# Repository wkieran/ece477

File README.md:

# ece477

## mimidrums

## prototyping
(1) mic_tutorial : microphone + SD

    if button is pressed once (EXTI_GPIO), mic is recording.
    if button is pressed once more, mic stops recording. And save audio files into SD as wav file.

## docs

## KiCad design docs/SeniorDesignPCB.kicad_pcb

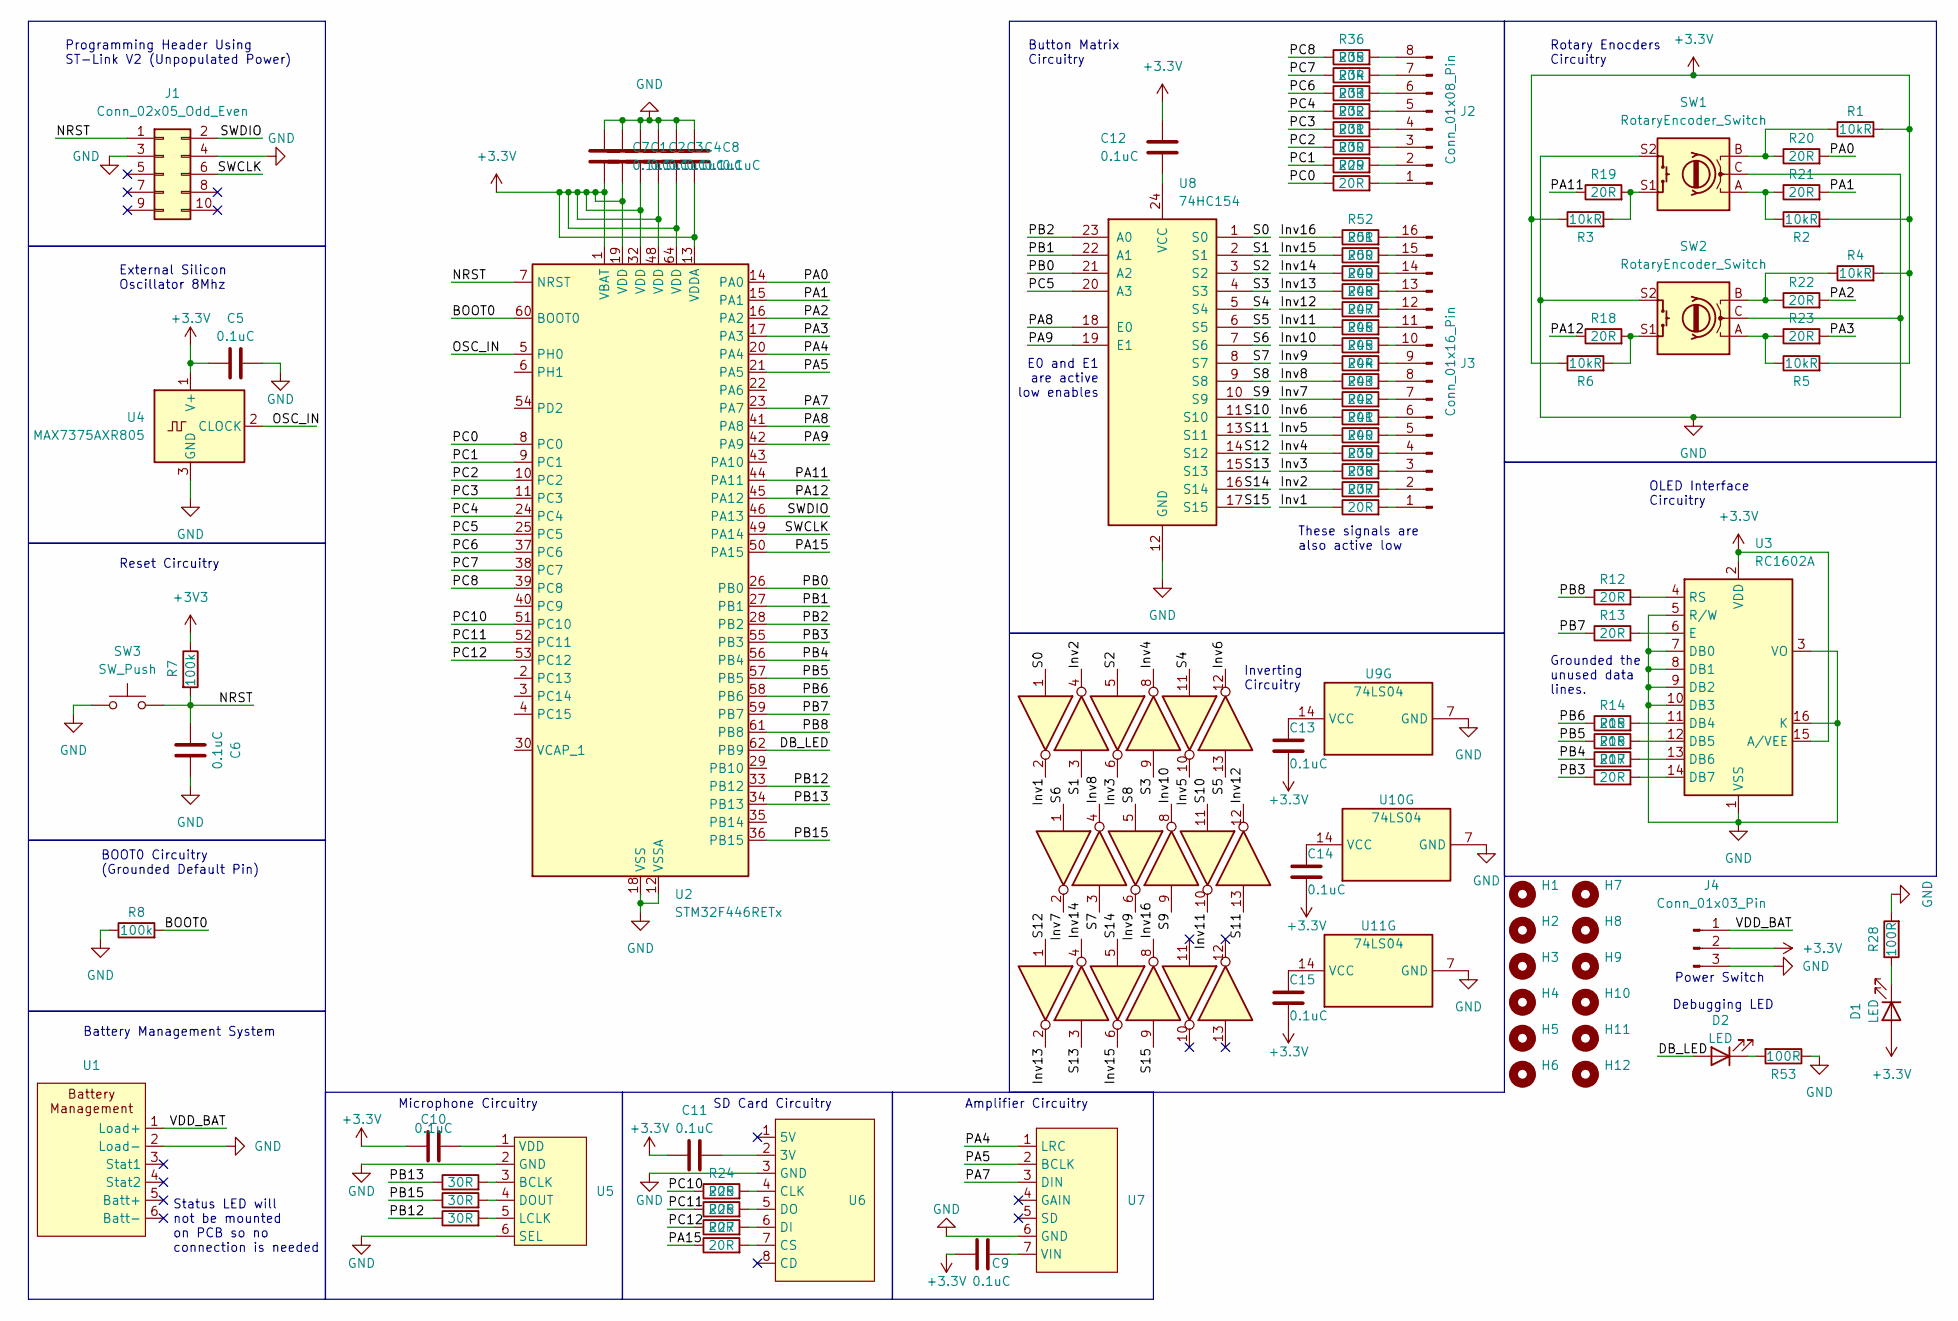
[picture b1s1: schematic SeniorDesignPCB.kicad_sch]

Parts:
C1, C2, C3, C4, C5, C6, C7, C8, C9, C10, C11, C12, C13, C14, C15: 0.1uC; C_0805_2012Metric_Pad1.18x1.45mm_HandSolder
D1: LED; D_5KP_P7.62mm_Vertical_AnodeUp
D2: LED; D_0805_2012Metric
H1, H2, H3, H4, H5, H6, H7, H8: MountingHole; MountingHole_2.2mm_M2
H9, H10, H11, H12: MountingHole; MountingHole_2.5mm
J1: Conn_02x05_Odd_Even; PinHeader_2x05_P2.54mm_Vertical
J2: Conn_01x08_Pin; PinHeader_1x08_P2.54mm_Vertical
J3: Conn_01x16_Pin; PinHeader_1x16_P2.54mm_Vertical
J4: Conn_01x03_Pin; PinHeader_1x03_P2.54mm_Vertical
R1, R2, R3, R4, R5, R6: 10kR; R_0805_2012Metric_Pad1.20x1.40mm_HandSolder
R7, R8: 100k; R_0805_2012Metric_Pad1.20x1.40mm_HandSolder
R9, R10, R11: 30R; R_0805_2012Metric_Pad1.20x1.40mm_HandSolder
R12, R13, R14, R15, R16, R17, R18, R19, R20, R21, R22, R23, R24, R25, R26, R27, R29, R30, R31, R32, R33, R34, R35, R36, R37, R38, R39, R40, R41, R42, R43, R44, R45, R46, R47, R48, R49, R50, R51, R52: 20R; R_0805_2012Metric_Pad1.20x1.40mm_HandSolder
R28, R53: 100R; R_0805_2012Metric_Pad1.20x1.40mm_HandSolder
SW1, SW2: RotaryEncoder_Switch; RotaryEncoder_Alps_EC11E-Switch_Vertical_H20mm
SW3: SW_Push; SW_Push_1P1T_NO_6x6mm_H9.5mm
U1, U5: PinHeader_1x06_P2.54mm_Vertical
U2: STM32F446RETx; LQFP-64_10x10mm_P0.5mm
U3: RC1602A; PinHeader_1x16_P2.54mm_Vertical
U4: MAX7375AXR805; SOT-323_SC-70
U6: PinHeader_1x08_P2.54mm_Vertical
U7: PinHeader_1x07_P2.54mm_Vertical
U8: 74HC154; DIP-24_W7.62mm
U9, U10, U11: 74LS04; DIP-14_W7.62mm

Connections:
+3.3V: C1.2, C2.2, C3.2, C4.2, C5.1, C7.2, C8.2, C9.1, C10.1, C11.1, C12.1, C13.2, C14.2, C15.2, D1.2 (A), J4.2, R1.2, R2.2, R3.1, R4.2, R5.2, R6.1, U2.1 (VBAT), U2.13 (VDDA), U2.19 (VDD), U2.32 (VDD), U2.48 (VDD), U2.64 (VDD), U3.2 (VDD), U3.15 (A/VEE), U4.1 (V+)
+3V3: R7.1
/BOOT0: R8.2, U2.60 (BOOT0)
/DB_LED: D2.2 (A), U2.62 (PB9)
/Inv1: R37.1, U9.2
/Inv2: R38.1, U9.4
/Inv3: R39.1, U9.6
/Inv4: R40.1, U9.8
/Inv5: R41.1, U9.10
/Inv6: R42.1, U9.12
/Inv7: R43.1, U10.2
/Inv8: R44.1, U10.4
/Inv9: R45.1, U10.6
/Inv10: R46.1, U10.8
/Inv11: R47.1, U10.10
/Inv12: R48.1, U10.12
/Inv13: R49.1, U11.2
/Inv14: R50.1, U11.4
/Inv15: R51.1, U11.6
/Inv16: R52.1, U11.8
/NRST: C6.1, J1.1, R7.2, SW3.2, U2.7 (NRST)
/OSC_IN: U2.5 (PH0), U4.2 (CLOCK)
/PA0: R20.2, U2.14 (PA0)
/PA1: R21.2, U2.15 (PA1)
/PA2: R22.2, U2.16 (PA2)
/PA3: R23.2, U2.17 (PA3)
/PA4: U2.20 (PA4), U7.1 (LRC)
/PA5: U2.21 (PA5), U7.2 (BCLK)
/PA7: U2.23 (PA7), U7.3 (DIN)
/PA8: U2.41 (PA8), U8.18 (E0)
/PA9: U2.42 (PA9), U8.19 (E1)
/PA11: R19.1, U2.44 (PA11)
/PA12: R18.1, U2.45 (PA12)
/PA15: R27.1, U2.50 (PA15)
/PB0: U2.26 (PB0), U8.21 (A2)
/PB1: U2.27 (PB1), U8.22 (A1)
/PB2: U2.28 (PB2), U8.23 (A0)
/PB3: R17.1, U2.55 (PB3)
/PB4: R16.1, U2.56 (PB4)
/PB5: R15.1, U2.57 (PB5)
/PB6: R14.1, U2.58 (PB6)
/PB7: R13.1, U2.59 (PB7)
/PB8: R12.1, U2.61 (PB8)
/PB12: R11.1, U2.33 (PB12)
/PB13: R9.1, U2.34 (PB13)
/PB15: R10.1, U2.36 (PB15)
/PC0: R29.1, U2.8 (PC0)
/PC1: R30.1, U2.9 (PC1)
/PC2: R31.1, U2.10 (PC2)
/PC3: R32.1, U2.11 (PC3)
/PC4: R33.1, U2.24 (PC4)
/PC5: U2.25 (PC5), U8.20 (A3)
/PC6: R34.1, U2.37 (PC6)
/PC7: R35.1, U2.38 (PC7)
/PC8: R36.1, U2.39 (PC8)
/PC10: R24.1, U2.51 (PC10)
/PC11: R25.1, U2.52 (PC11)
/PC12: R26.1, U2.53 (PC12)
/S0: U8.1 (S0), U9.1
/S1: U8.2 (S1), U9.3
/S2: U8.3 (S2), U9.5
/S3: U8.4 (S3), U9.9
/S4: U8.5 (S4), U9.11
/S5: U8.6 (S5), U9.13
/S6: U8.7 (S6), U10.1
/S7: U8.8 (S7), U10.3
/S8: U8.9 (S8), U10.5
/S9: U8.10 (S9), U10.9
/S10: U8.11 (S10), U10.11
/S11: U8.13 (S11), U10.13
/S12: U8.14 (S12), U11.1
/S13: U8.15 (S13), U11.3
/S14: U8.16 (S14), U11.5
/S15: U8.17 (S15), U11.9
/SWCLK: J1.6, U2.49 (PA14)
/SWDIO: J1.2, U2.46 (PA13)
/VDD_BAT: J4.1, U1.1 (Load+)
GND: C1.1, C2.1, C3.1, C4.1, C5.2, C6.2, C7.1, C8.1, J1.3, J1.4, J4.3, R8.1, R28.2, R53.1, SW1.C, SW1.S2, SW2.C, SW2.S2, SW3.1, U1.2 (Load-), U2.12 (VSSA), U2.18 (VSS), U2.31 (VSS), U2.47 (VSS), U2.63 (VSS), U3.1 (VSS), U3.3 (VO), U3.5 (R/W), U3.7 (DB0), U3.8 (DB1), U3.9 (DB2), U3.10 (DB3), U3.16 (K), U4.3 (GND), U5.2 (GND), U5.6 (SEL), U6.3 (GND), U7.6 (GND), U8.12 (GND), U9.7 (GND), U10.7 (GND), U11.7 (GND)
unnamed: D1.1 (K), R28.1
unnamed: D2.1 (K), R53.2
unnamed: J2.1, R29.2
unnamed: J2.2, R30.2
unnamed: J2.3, R31.2
unnamed: J2.4, R32.2
unnamed: J2.5, R33.2
unnamed: J2.6, R34.2
unnamed: J2.7, R35.2
unnamed: J2.8, R36.2
unnamed: J3.1, R37.2
unnamed: J3.2, R38.2
unnamed: J3.3, R39.2
unnamed: J3.4, R40.2
unnamed: J3.5, R41.2
unnamed: J3.6, R42.2
unnamed: J3.7, R43.2
unnamed: J3.8, R44.2
unnamed: J3.9, R45.2
unnamed: J3.10, R46.2
unnamed: J3.11, R47.2
unnamed: J3.12, R48.2
unnamed: J3.13, R49.2
unnamed: J3.14, R50.2
unnamed: J3.15, R51.2
unnamed: J3.16, R52.2
unnamed: R1.1, R20.1, SW1.B
unnamed: R2.1, R21.1, SW1.A
unnamed: R6.2, R18.2, SW2.S1
unnamed: R3.2, R19.2, SW1.S1
unnamed: R4.1, R22.1, SW2.B
unnamed: R5.1, R23.1, SW2.A
unnamed: R14.2, U3.11 (DB4)
unnamed: R15.2, U3.12 (DB5)
unnamed: R16.2, U3.13 (DB6)
unnamed: R17.2, U3.14 (DB7)
unnamed: R13.2, U3.6 (E)
unnamed: R12.2, U3.4 (RS)
unnamed: R9.2, U5.3 (BCLK)
unnamed: R10.2, U5.4 (DOUT)
unnamed: R11.2, U5.5 (LCLK)
unnamed: C10.2, U5.1 (VDD)
unnamed: C11.2, U6.2 (3V)
unnamed: R24.2, U6.4 (CLK)
unnamed: R27.2, U6.7 (CS)
unnamed: R26.2, U6.6 (DI)
unnamed: R25.2, U6.5 (DO)
unnamed: C9.2, U7.7 (VIN)
unnamed: C12.2, U8.24 (VCC)
unnamed: C13.1, U9.14 (VCC)
unnamed: C14.1, U10.14 (VCC)
unnamed: C15.1, U11.14 (VCC)

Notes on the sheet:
External Silicon Oscillator 8Mhz
Power Switch
Amplifier Circuitry
Status LED will not be mounted on PCB so no connection is needed
Rotary Enocders Circuitry
SD Card Circuitry
Reset Circuitry
Grounded the unused data lines.
Debugging LED
Battery Management System
Microphone Circuitry
E0 and E1 are active low enables
Inverting Circuitry
Button Matrix Circuitry
Programming Header Using ST-Link V2 (Unpopulated Power)
These signals are also active low
BOOT0 Circuitry (Grounded Default Pin)
OLED Interface Circuitry

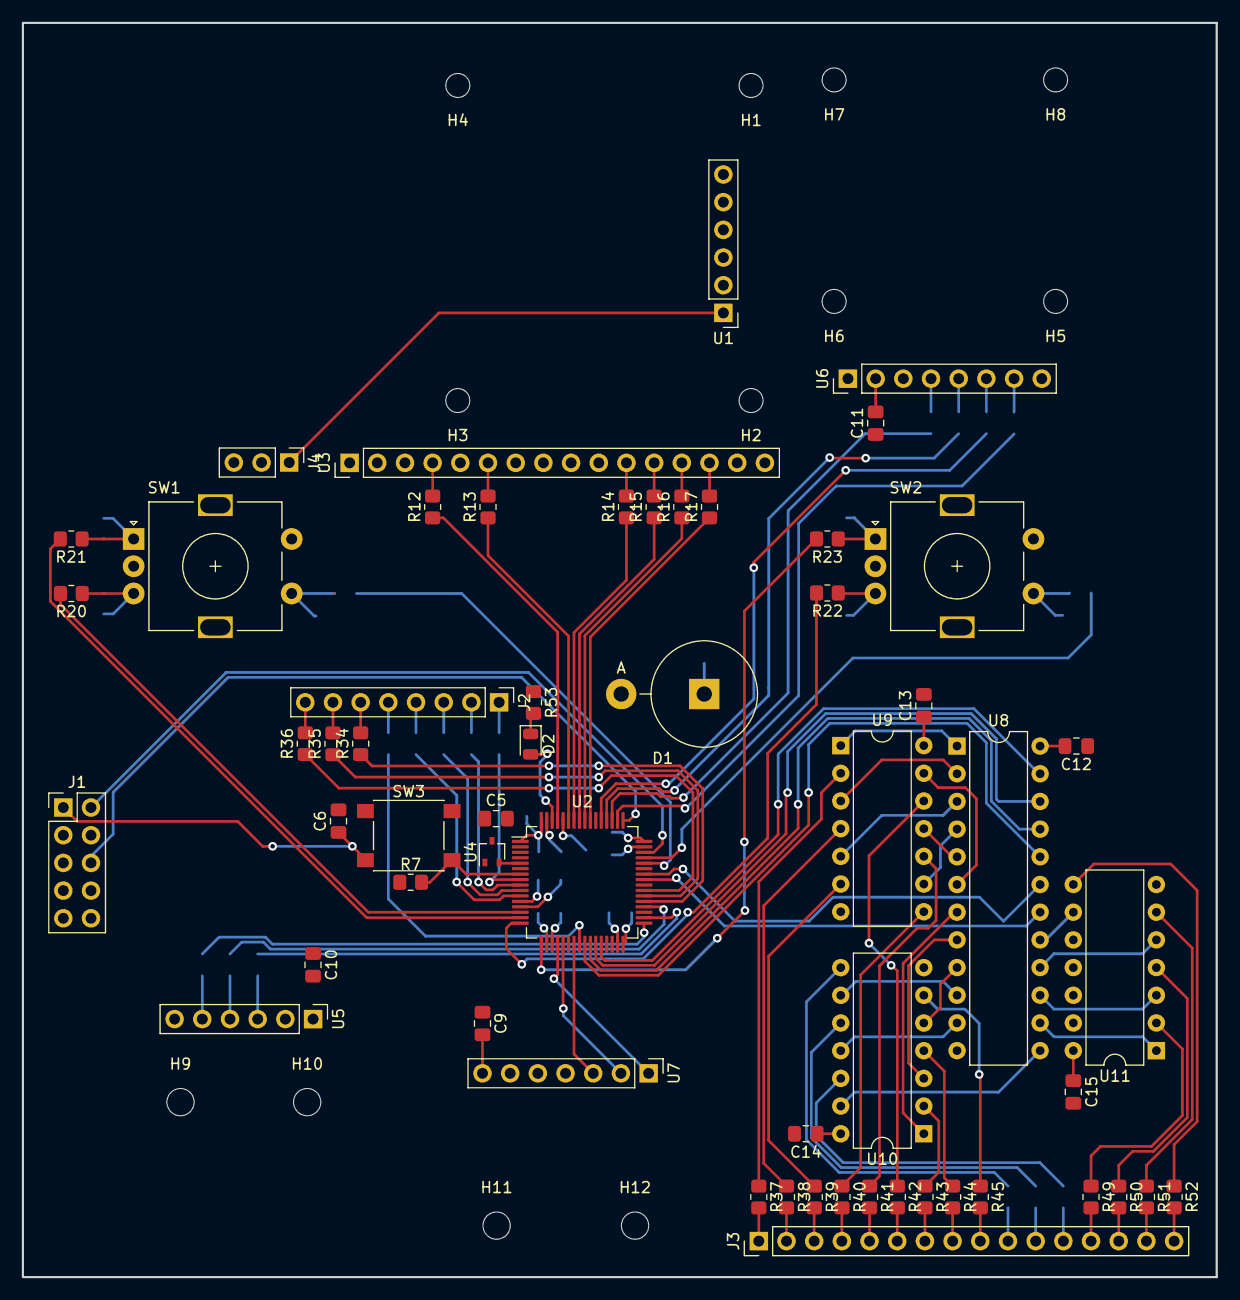
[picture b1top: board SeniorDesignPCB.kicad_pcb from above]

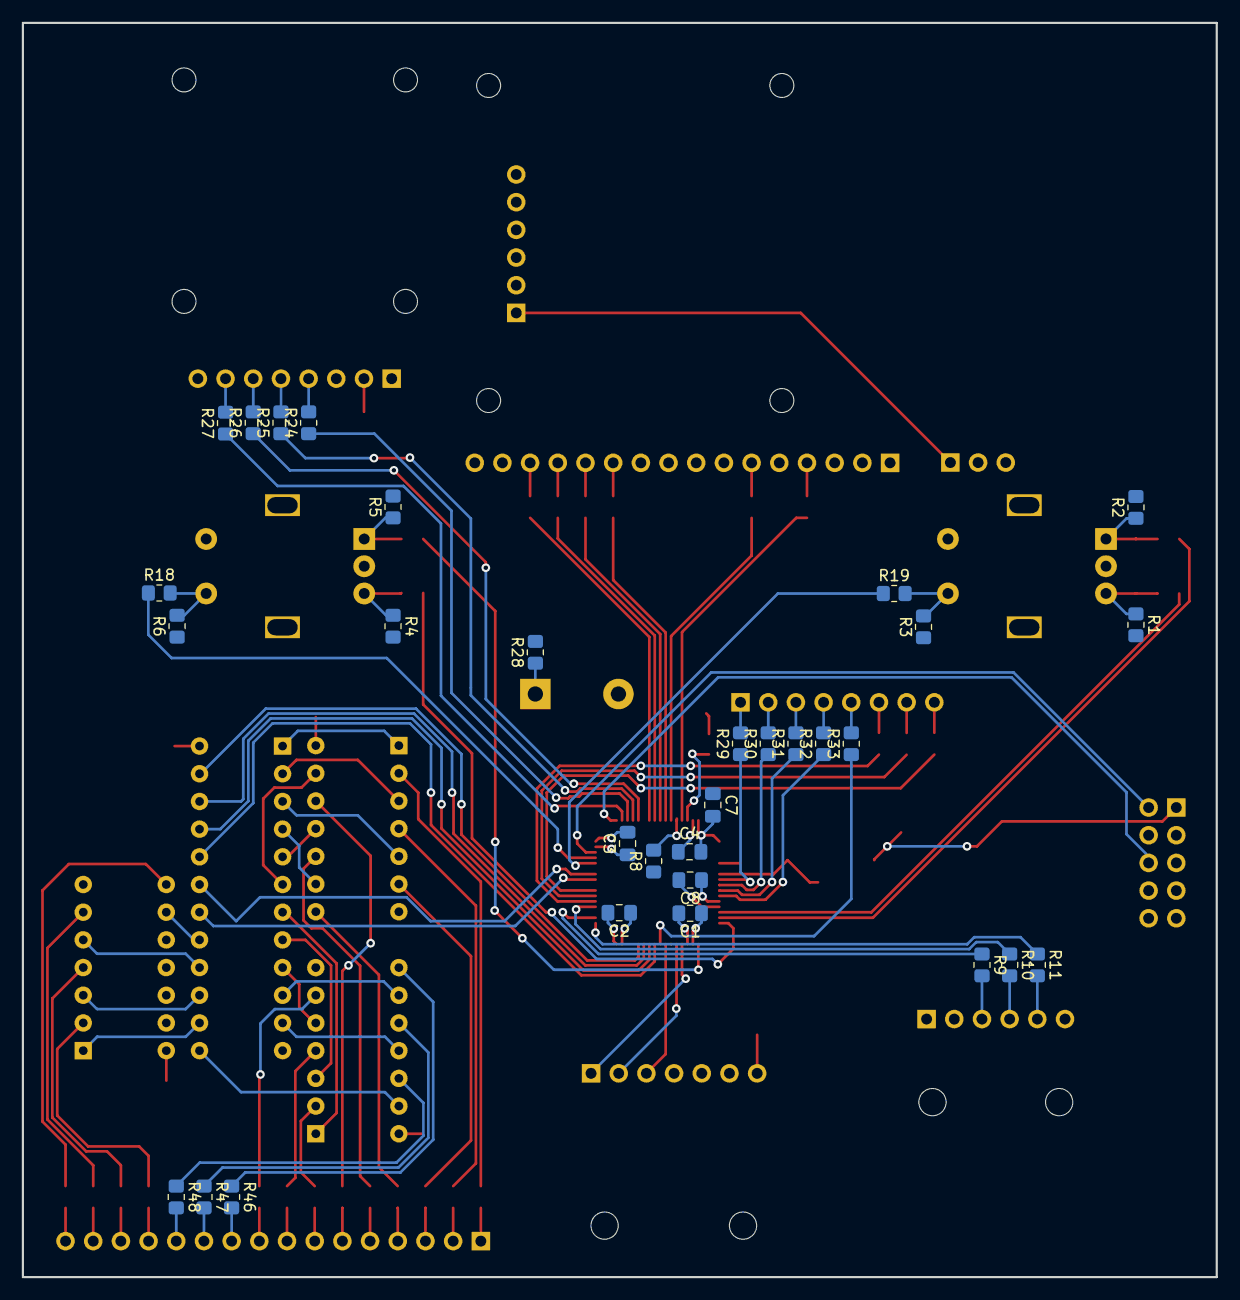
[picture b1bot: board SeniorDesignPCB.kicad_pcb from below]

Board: 2 copper layers, 109.5 x 115.1 mm, 100 parts (31 on the bottom side), 129 nets.

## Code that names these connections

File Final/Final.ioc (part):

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Mcu.Name=STM32F446R(C-E)Tx
Mcu.Package=LQFP64
Mcu.UserName=STM32F446RETx
PA0-WKUP.Signal=S_TIM2_CH1_ETR
PA1.Signal=S_TIM2_CH2
PA11.GPIOParameters=GPIO_Label
PA11.GPIO_Label=push1
PA11.Signal=GPXTI11
PA12.GPIOParameters=GPIO_Label
PA12.GPIO_Label=push2
PA12.Signal=GPXTI12
PA8.GPIOParameters=GPIO_Label
PA8.GPIO_Label=E0
PA8.Signal=GPIO_Output
PA9.GPIOParameters=GPIO_Label
PA9.GPIO_Label=E1
PA9.Signal=GPIO_Output
PB0.GPIOParameters=GPIO_Label
PB0.GPIO_Label=A2
PB0.Signal=GPIO_Output
PB1.GPIOParameters=GPIO_Label
PB1.GPIO_Label=A1
PB1.Signal=GPIO_Output
PB2.GPIOParameters=GPIO_Label
PB2.GPIO_Label=A0
PB2.Signal=GPIO_Output
PB7.Mode=I2C
PB7.Signal=I2C1_SDA
PB8.Mode=I2C
PB8.Signal=I2C1_SCL
PB9.Signal=GPIO_Output
PC0.GPIOParameters=GPIO_Label
PC0.GPIO_Label=Kout3
PC0.Signal=GPIO_Output
PC1.GPIOParameters=GPIO_Label
PC1.GPIO_Label=Kout2
PC1.Signal=GPIO_Output
PC2.GPIOParameters=GPIO_Label
PC2.GPIO_Label=Kout1
PC2.Signal=GPIO_Output
PC3.GPIOParameters=GPIO_Label
PC3.GPIO_Label=Kout0
PC3.Signal=GPIO_Output
PC4.GPIOParameters=GPIO_PuPd,GPIO_Label
PC4.GPIO_Label=Kin0
PC4.GPIO_PuPd=GPIO_PULLUP
PC4.Signal=GPIO_Input
PC5.GPIOParameters=GPIO_Label
PC5.GPIO_Label=A3
PC5.Signal=GPIO_Output
PC6.GPIOParameters=GPIO_PuPd,GPIO_Label
PC6.GPIO_Label=Kin1
PC6.GPIO_PuPd=GPIO_PULLUP
PC6.Signal=GPIO_Input
PC7.GPIOParameters=GPIO_PuPd,GPIO_Label
PC7.GPIO_Label=Kin2
PC7.GPIO_PuPd=GPIO_PULLUP
PC7.Signal=GPIO_Input
PC8.GPIOParameters=GPIO_PuPd,GPIO_Label
PC8.GPIO_Label=Kin3
PC8.GPIO_PuPd=GPIO_PULLUP
PC8.Signal=GPIO_Input
PH0-OSC_IN.Mode=HSE-External-Oscillator
PH0-OSC_IN.Signal=RCC_OSC_IN
PH1-OSC_OUT.Mode=HSE-External-Oscillator
PH1-OSC_OUT.Signal=RCC_OSC_OUT
RCC.HSE_VALUE=8000000
RCC.SYSCLKFreq_VALUE=90000000
RCC.SYSCLKSource=RCC_SYSCLKSOURCE_PLLCLK
board=custom

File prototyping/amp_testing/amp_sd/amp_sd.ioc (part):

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Mcu.Name=STM32F446R(C-E)Tx
Mcu.Package=LQFP64
Mcu.UserName=STM32F446RETx
PA13.GPIOParameters=GPIO_Label
PA13.GPIO_Label=TMS
PA13.Signal=SYS_JTMS-SWDIO
PA14.GPIOParameters=GPIO_Label
PA14.GPIO_Label=TCK
PA14.Signal=SYS_JTCK-SWCLK
PA15.Signal=SPI3_NSS
PA2.GPIOParameters=GPIO_Label
PA2.GPIO_Label=USART_TX
PA2.Signal=USART2_TX
PA3.GPIOParameters=GPIO_Label
PA3.GPIO_Label=USART_RX
PA3.Signal=USART2_RX
PA4.Mode=Half_Duplex_Master
PA4.Signal=I2S1_WS
PA5.Mode=Half_Duplex_Master
PA5.Signal=I2S1_CK
PA7.Mode=Half_Duplex_Master
PA7.Signal=I2S1_SD
PA8.Signal=GPIO_Input
PB12.Mode=Half_Duplex_Master
PB12.Signal=I2S2_WS
PB13.Mode=Half_Duplex_Master
PB13.Signal=I2S2_CK
PB15.Mode=Half_Duplex_Master
PB15.Signal=I2S2_SD
PB3.GPIOParameters=GPIO_Label
PB3.GPIO_Label=SWO
PB3.Signal=SYS_JTDO-SWO
PC10.Mode=Full_Duplex_Master
PC10.Signal=SPI3_SCK
PC11.Mode=Full_Duplex_Master
PC11.Signal=SPI3_MISO
PC12.Mode=Full_Duplex_Master
PC12.Signal=SPI3_MOSI
PC13.GPIOParameters=GPIO_Label,GPIO_ModeDefaultEXTI
PC13.GPIO_Label=B1 [Blue PushButton]
PC13.GPIO_ModeDefaultEXTI=GPIO_MODE_IT_FALLING
PC13.Signal=GPXTI13
PC14-OSC32_IN.Signal=RCC_OSC32_IN
PC15-OSC32_OUT.Signal=RCC_OSC32_OUT
PC9.Signal=GPIO_Output
PH0-OSC_IN.Signal=RCC_OSC_IN
PH1-OSC_OUT.Signal=RCC_OSC_OUT
RCC.HSE_VALUE=8000000
RCC.SYSCLKFreq_VALUE=84000000
RCC.SYSCLKSource=RCC_SYSCLKSOURCE_PLLCLK
board=NUCLEO-F446RE
boardIOC=true

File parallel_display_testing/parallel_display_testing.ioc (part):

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Mcu.Name=STM32F446R(C-E)Tx
Mcu.Package=LQFP64
Mcu.UserName=STM32F446RETx
PA6.Signal=GPIO_Output
PA7.Signal=GPIO_Output
PB4.Signal=GPIO_Output
PB5.Signal=GPIO_Output
PB6.Signal=GPIO_Output
PC7.Signal=GPIO_Output
board=custom

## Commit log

2023-09-08 Rotary Encoder File for STM32 Workbench
2023-09-12 Create ece362labs
2023-09-12 adding old 362 lab code for OLED
2023-09-12 CubeIDE file for rotary encoder
2023-09-14 Create d
2023-09-17 updated by Jane
2023-09-25 uploading semi working display code
2023-09-25 reorganizing and update README
2023-09-26 added main CubeIDE project
2023-09-27 mysterious :3
2023-09-29 attempt at interfacing with the speaker
2023-10-03 Create cc
2023-10-04 added SD card testing code
2023-10-06 Sequencer code with AudioFile
    Need mem test
2023-10-11 reorganize lol
2023-10-11 lazy
2023-11-06 adding working mic and sd code
2023-11-17 Create Final
2023-11-17 Create Final direc
2023-11-17 Adding src, inc, and ioc files for final build
2023-11-28 adding code for 3rd PSDR
2023-11-28 the fourth psdr
2023-11-29 Create createfolder
    creating recording directory
